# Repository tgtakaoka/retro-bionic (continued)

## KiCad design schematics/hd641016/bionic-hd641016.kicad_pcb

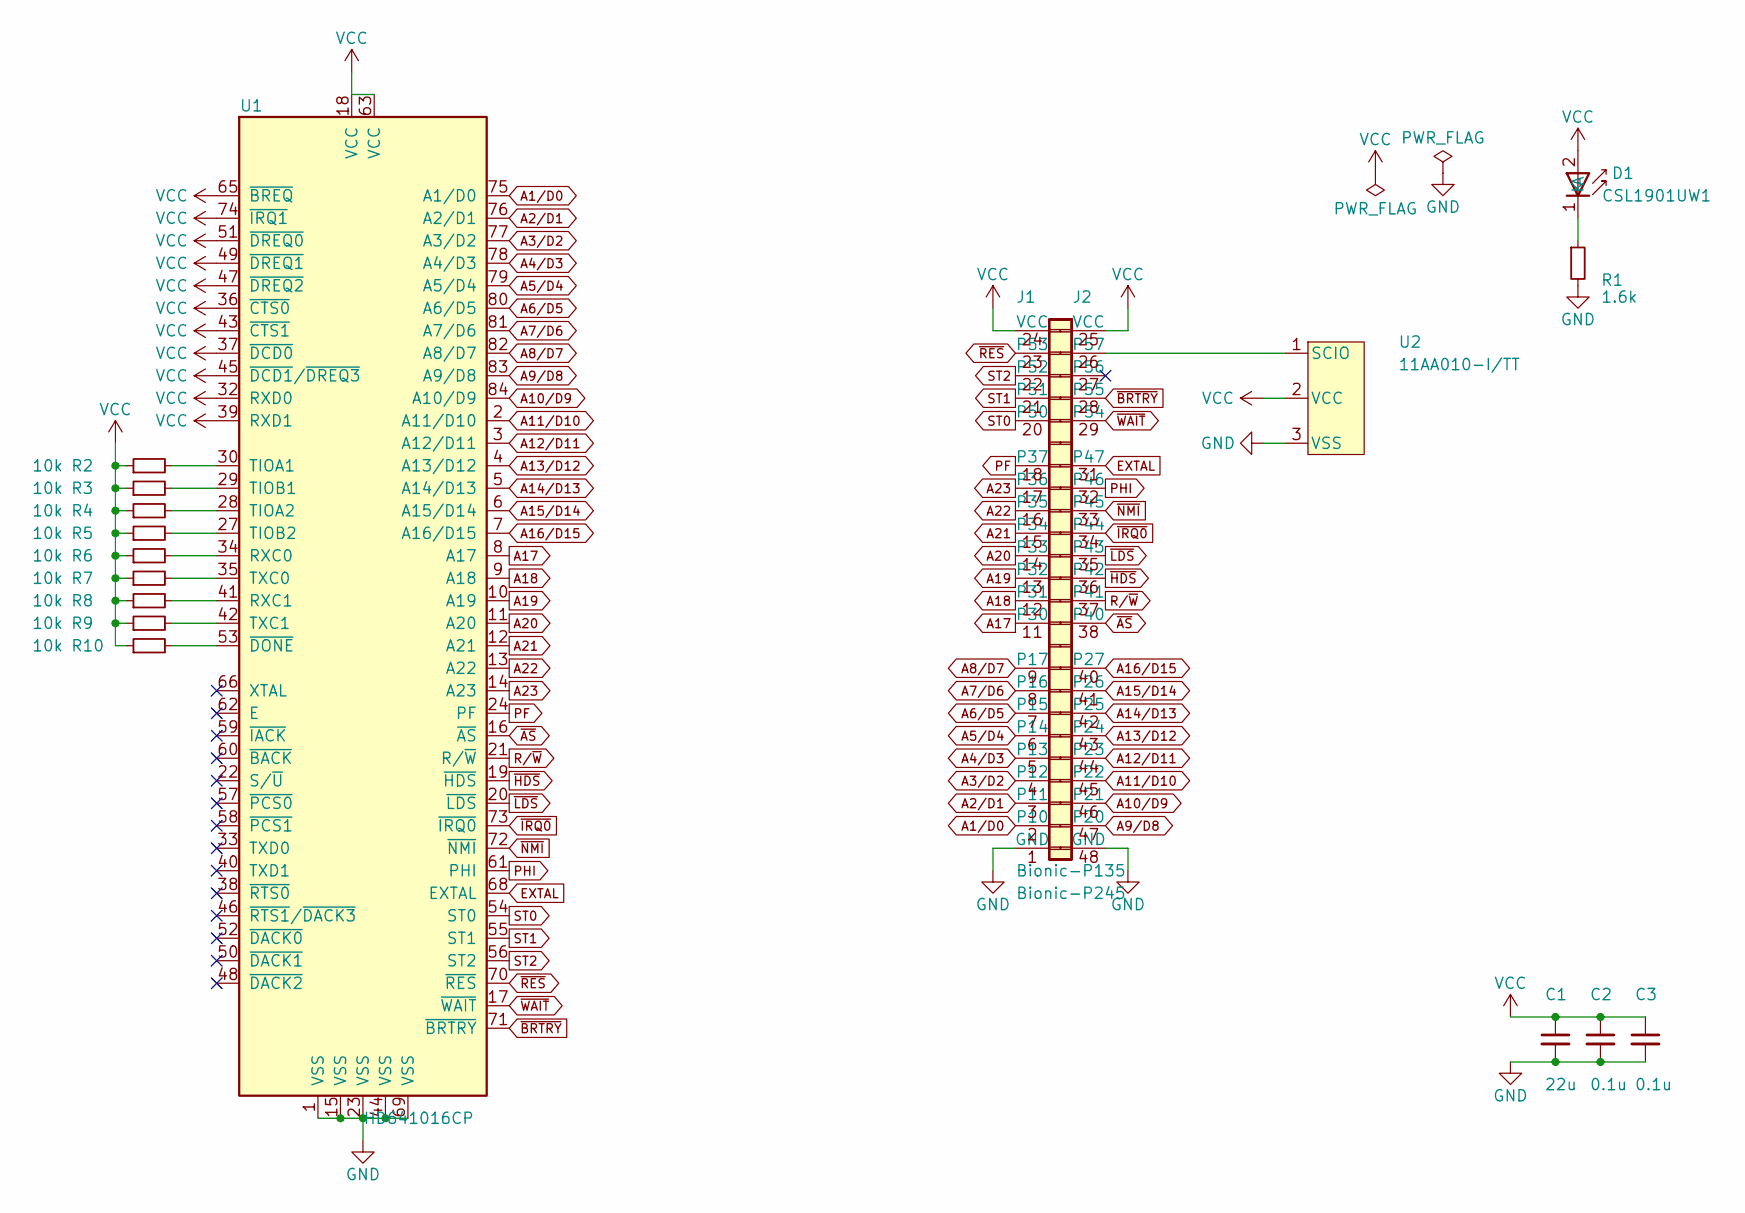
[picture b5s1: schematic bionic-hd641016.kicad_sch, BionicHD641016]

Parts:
C1: 22u; C_0603_1608Metric_Pad1.08x0.95mm_HandSolder
C2, C3: 0.1u; C_0603_1608Metric_Pad1.08x0.95mm_HandSolder
D1: CSL1901UW1; LED_CSL1901UW1_ROM-M
J1: Bionic-P135; Bionic-P135_SMT
J2: Bionic-P245; Bionic-P245_SMT
R1: 1.6k; R_0603_1608Metric_Pad0.98x0.95mm_HandSolder
R2, R3, R4, R5, R6, R7, R8, R9, R10: 10k; R_0603_1608Metric_Pad0.98x0.95mm_HandSolder
U1: HD641016CP; 848421B1RKTP
U2: 11AA010-I/TT; SOT-23_MC_MCH-M

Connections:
A1/D0: J1.2 (P10), U1.75 (A1/D0)
A2/D1: J1.3 (P11), U1.76 (A2/D1)
A3/D2: J1.4 (P12), U1.77 (A3/D2)
A4/D3: J1.5 (P13), U1.78 (A4/D3)
A5/D4: J1.6 (P14), U1.79 (A5/D4)
A6/D5: J1.7 (P15), U1.80 (A6/D5)
A7/D6: J1.8 (P16), U1.81 (A7/D6)
A8/D7: J1.9 (P17), U1.82 (A8/D7)
A9/D8: J2.47 (P20), U1.83 (A9/D8)
A10/D9: J2.46 (P21), U1.84 (A10/D9)
A11/D10: J2.45 (P22), U1.2 (A11/D10)
A12/D11: J2.44 (P23), U1.3 (A12/D11)
A13/D12: J2.43 (P24), U1.4 (A13/D12)
A14/D13: J2.42 (P25), U1.5 (A14/D13)
A15/D14: J2.41 (P26), U1.6 (A15/D14)
A16/D15: J2.40 (P27), U1.7 (A16/D15)
A17: J1.11 (P30), U1.8 (A17)
A18: J1.12 (P31), U1.9 (A18)
A19: J1.13 (P32), U1.10 (A19)
A20: J1.14 (P33), U1.11 (A20)
A21: J1.15 (P34), U1.12 (A21)
A22: J1.16 (P35), U1.13 (A22)
A23: J1.17 (P36), U1.14 (A23)
EXTAL: J2.31 (P47), U1.68 (EXTAL)
GND: C1.2, C2.2, C3.2, J1.1 (GND), J2.48 (GND), R1.2, U1.1 (VSS), U1.15 (VSS), U1.23 (VSS), U1.44 (VSS), U1.69 (VSS), U2.3 (VSS)
unnamed: D1.1 (K), R1.1
unnamed: J2.26 (P57), U2.1 (SCIO)
unnamed: R6.2, U1.34 (RXC0)
unnamed: R8.2, U1.41 (RXC1)
unnamed: R2.2, U1.30 (TIOA1)
unnamed: R4.2, U1.28 (TIOA2)
unnamed: R3.2, U1.29 (TIOB1)
unnamed: R5.2, U1.27 (TIOB2)
unnamed: R7.2, U1.35 (TXC0)
unnamed: R9.2, U1.42 (TXC1)
unnamed: R10.2, U1.53 (~DONE)
PF: J1.18 (P37), U1.24 (PF)
PHI: J2.32 (P46), U1.61 (PHI)
R/~W: J2.37 (P41), U1.21 (R/~W)
ST0: J1.20 (P50), U1.54 (ST0)
ST1: J1.21 (P51), U1.55 (ST1)
ST2: J1.22 (P52), U1.56 (ST2)
VCC: C1.1, C2.1, C3.1, D1.2 (A), J1.24 (VCC), J2.25 (VCC), R2.1, R3.1, R4.1, R5.1, R6.1, R7.1, R8.1, R9.1, R10.1, U1.18 (VCC), U1.32 (RXD0), U1.36 (~CTS0), U1.37 (~DCD0), U1.39 (RXD1), U1.43 (~CTS1), U1.45 (~DCD1/~DREQ3), U1.47 (~DREQ2), U1.49 (~DREQ1), U1.51 (~DREQ0), U1.63 (VCC), U1.65 (~BREQ), U1.74 (~IRQ1), U2.2 (VCC)
~AS: J2.38 (P40), U1.16 (~AS)
~BRTRY: J2.28 (P55), U1.71 (~BRTRY)
~HDS: J2.36 (P42), U1.19 (~HDS)
~IRQ0: J2.34 (P44), U1.73 (~IRQ0)
~LDS: J2.35 (P43), U1.20 (~LDS)
~NMI: J2.33 (P45), U1.72 (~NMI)
~RES: J1.23 (P53), U1.70 (~RES)
~WAIT: J2.29 (P54), U1.17 (~WAIT)

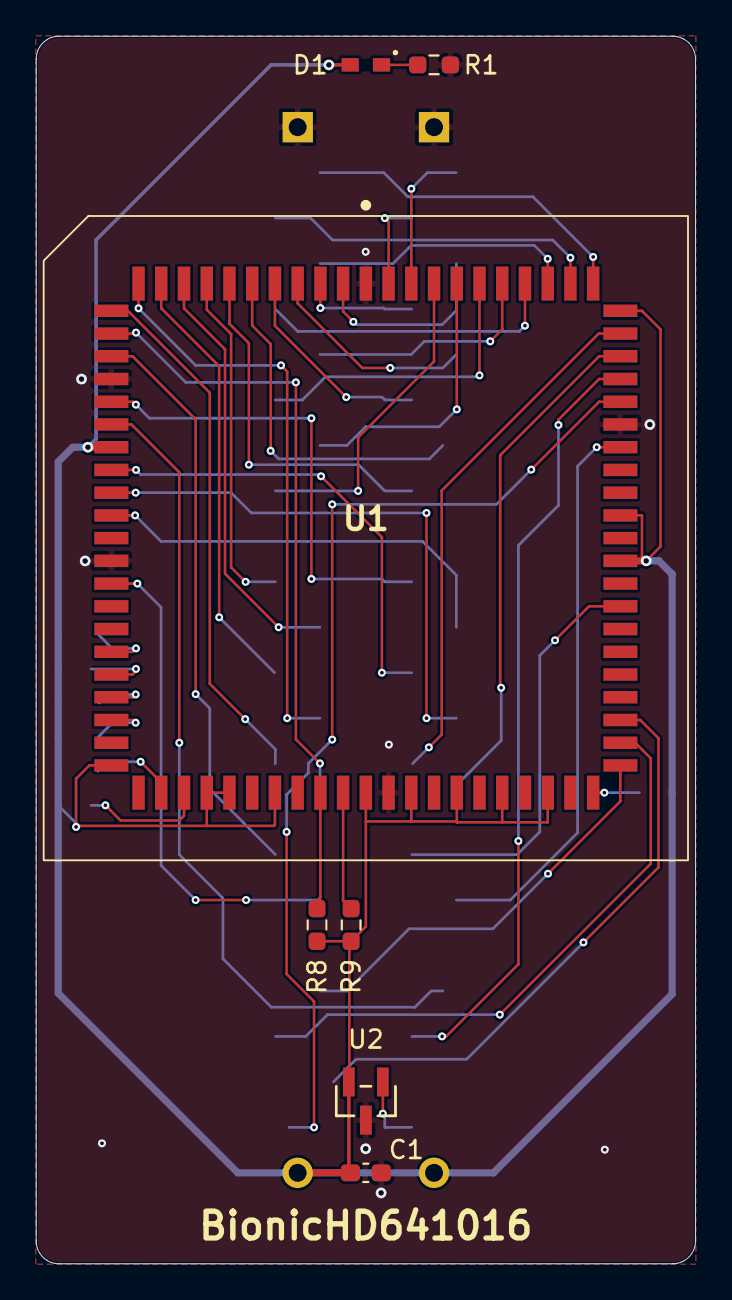
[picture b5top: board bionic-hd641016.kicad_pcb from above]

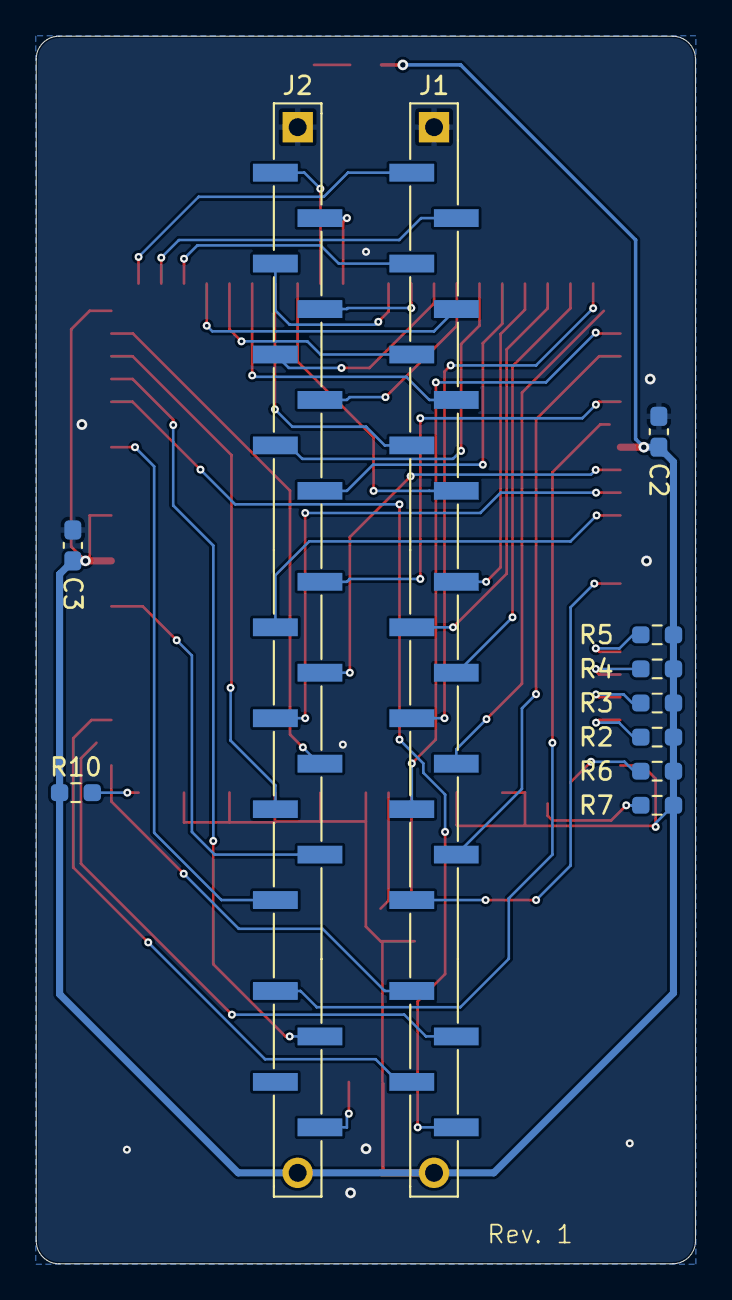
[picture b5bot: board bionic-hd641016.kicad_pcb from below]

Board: 2 copper layers, 36.8 x 68.6 mm, 18 parts (11 on the bottom side), 51 nets.

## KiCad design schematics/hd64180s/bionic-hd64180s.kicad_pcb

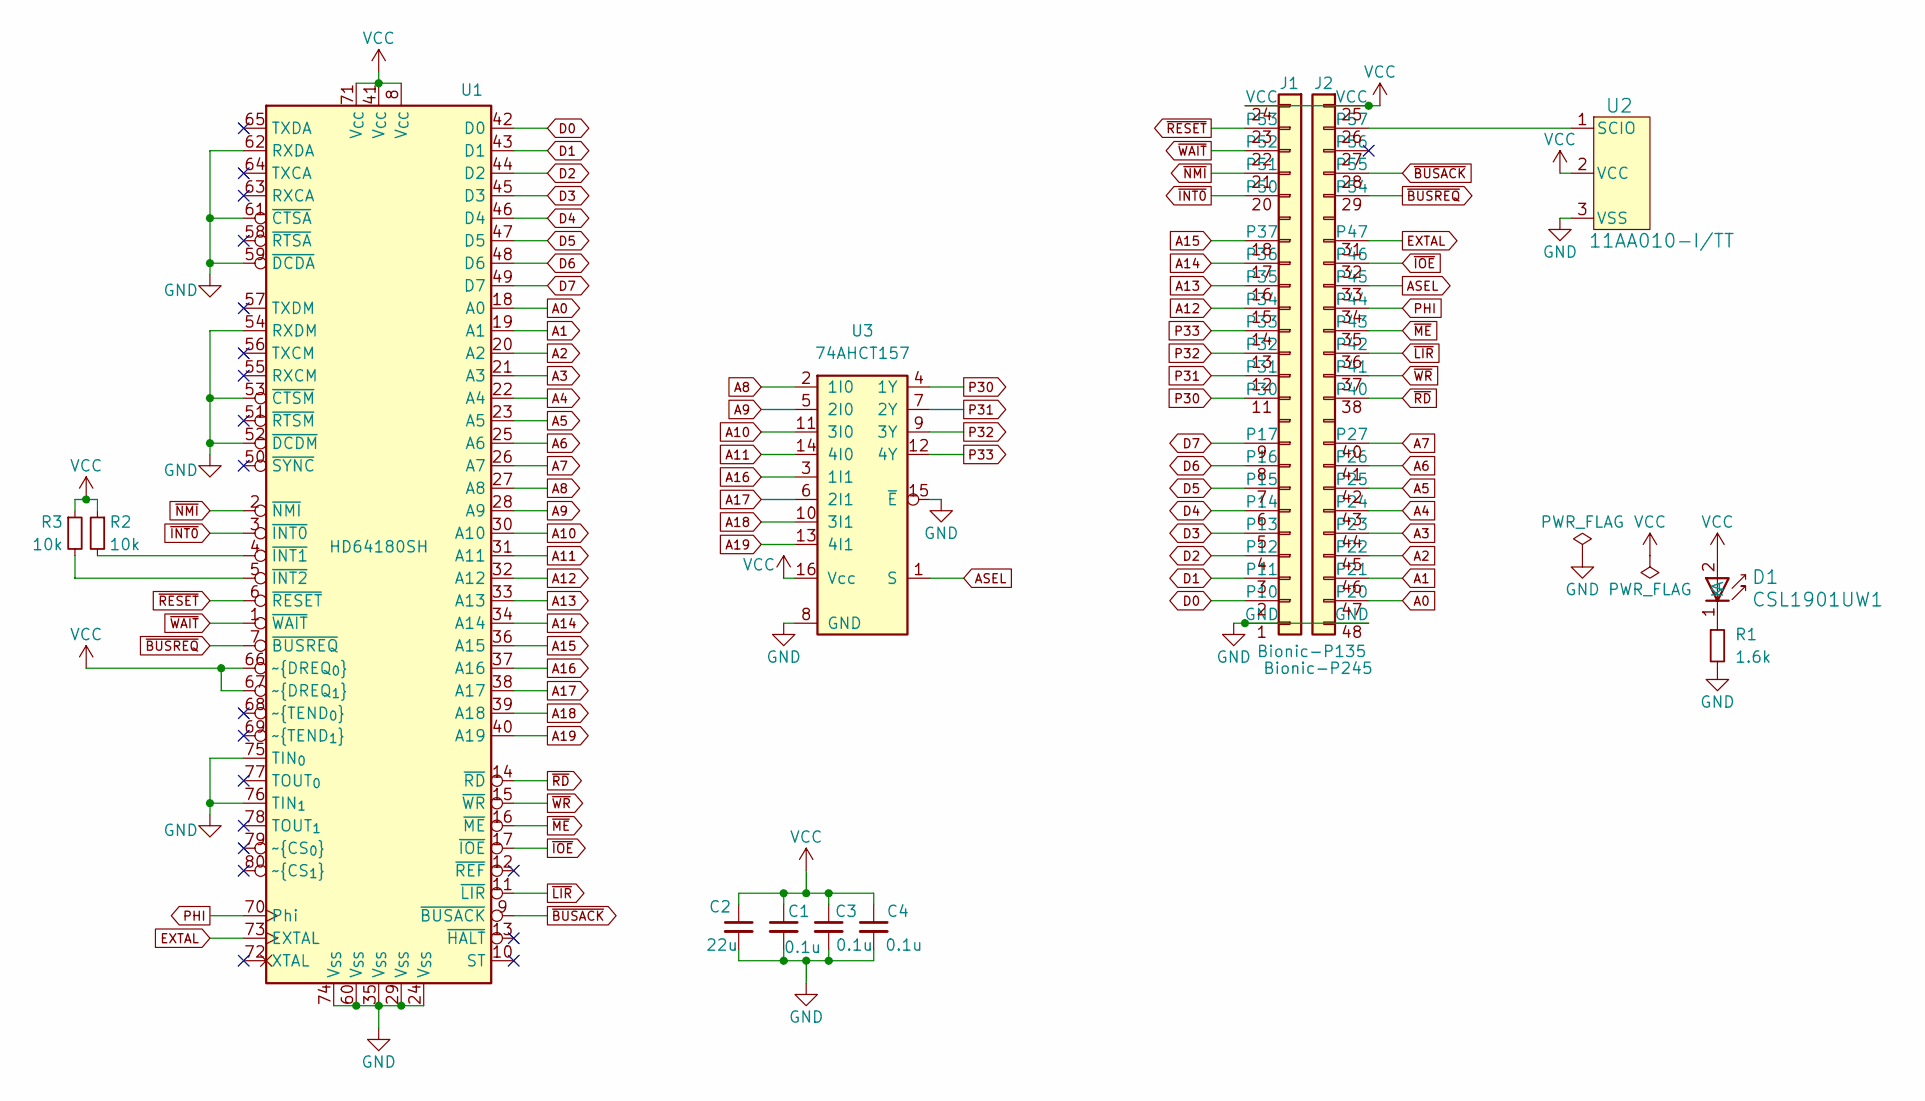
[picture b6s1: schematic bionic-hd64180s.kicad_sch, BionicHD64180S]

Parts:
C1, C3, C4: 0.1u; C_0603_1608Metric_Pad1.08x0.95mm_HandSolder
C2: 22u; C_0603_1608Metric_Pad1.08x0.95mm_HandSolder
D1: CSL1901UW1; LED_CSL1901UW1_ROM-M
J1: Bionic-P135; Bionic-P135_SMT
J2: Bionic-P245; Bionic-P245_SMT
R1: 1.6k; R_0603_1608Metric_Pad0.98x0.95mm_HandSolder
R2, R3: 10k; R_0603_1608Metric_Pad0.98x0.95mm_HandSolder
U1: HD64180SH; PQFP-80_14x14mm_P0.65mm
U2: 11AA010-I/TT; SOT-23_MC_MCH-M
U3: 74AHCT157; PW16-M

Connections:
A0: J2.47 (P20), U1.18 (A0)
A1: J2.46 (P21), U1.19 (A1)
A2: J2.45 (P22), U1.20 (A2)
A3: J2.44 (P23), U1.21 (A3)
A4: J2.43 (P24), U1.22 (A4)
A5: J2.42 (P25), U1.23 (A5)
A6: J2.41 (P26), U1.25 (A6)
A7: J2.40 (P27), U1.26 (A7)
A8: U1.27 (A8), U3.2 (1I0)
A9: U1.28 (A9), U3.5 (2I0)
A10: U1.30 (A10), U3.11 (3I0)
A11: U1.31 (A11), U3.14 (4I0)
A12: J1.15 (P34), U1.32 (A12)
A13: J1.16 (P35), U1.33 (A13)
A14: J1.17 (P36), U1.34 (A14)
A15: J1.18 (P37), U1.36 (A15)
A16: U1.37 (A16), U3.3 (1I1)
A17: U1.38 (A17), U3.6 (2I1)
A18: U1.39 (A18), U3.10 (3I1)
A19: U1.40 (A19), U3.13 (4I1)
ASEL: J2.33 (P45), U3.1 (S)
D0: J1.2 (P10), U1.42 (D0)
D1: J1.3 (P11), U1.43 (D1)
D2: J1.4 (P12), U1.44 (D2)
D3: J1.5 (P13), U1.45 (D3)
D4: J1.6 (P14), U1.46 (D4)
D5: J1.7 (P15), U1.47 (D5)
D6: J1.8 (P16), U1.48 (D6)
D7: J1.9 (P17), U1.49 (D7)
EXTAL: J2.31 (P47), U1.73 (EXTAL)
GND: C1.2, C2.2, C3.2, C4.2, J1.1 (GND), J2.48 (GND), R1.2, U1.24 (V_{SS}), U1.29 (V_{SS}), U1.35 (V_{SS}), U1.52 (~DCDM), U1.53 (~CTSM), U1.54 (RXDM), U1.59 (~DCDA), U1.60 (V_{SS}), U1.61 (~CTSA), U1.62 (RXDA), U1.74 (V_{SS}), U1.75 (TIN_{0}), U1.76 (TIN_{1}), U2.3 (VSS), U3.8 (GND), U3.15 (~E)
unnamed: D1.1 (K), R1.1
unnamed: J2.26 (P57), U2.1 (SCIO)
unnamed: R2.2, U1.4 (~INT1)
unnamed: R3.2, U1.5 (~INT2)
P30: J1.11 (P30), U3.4 (1Y)
P31: J1.12 (P31), U3.7 (2Y)
P32: J1.13 (P32), U3.9 (3Y)
P33: J1.14 (P33), U3.12 (4Y)
PHI: J2.34 (P44), U1.70 (Phi)
VCC: C1.1, C2.1, C3.1, C4.1, D1.2 (A), J1.24 (VCC), J2.25 (VCC), R2.1, R3.1, U1.8 (V_{CC}), U1.41 (V_{CC}), U1.66 (~DREQ_{0}), U1.67 (~DREQ_{1}), U1.71 (V_{CC}), U2.2 (VCC), U3.16 (Vcc)
~BUSACK: J2.28 (P55), U1.9 (~BUSACK)
~BUSREQ: J2.29 (P54), U1.7 (~BUSREQ)
~INT0: J1.20 (P50), U1.3 (~INT0)
~IOE: J2.32 (P46), U1.17 (~IOE)
~LIR: J2.36 (P42), U1.11 (~LIR)
~ME: J2.35 (P43), U1.16 (~ME)
~NMI: J1.21 (P51), U1.2 (~NMI)
~RD: J2.38 (P40), U1.14 (~RD)
~RESET: J1.23 (P53), U1.6 (~RESET)
~WAIT: J1.22 (P52), U1.1 (~WAIT)
~WR: J2.37 (P41), U1.15 (~WR)

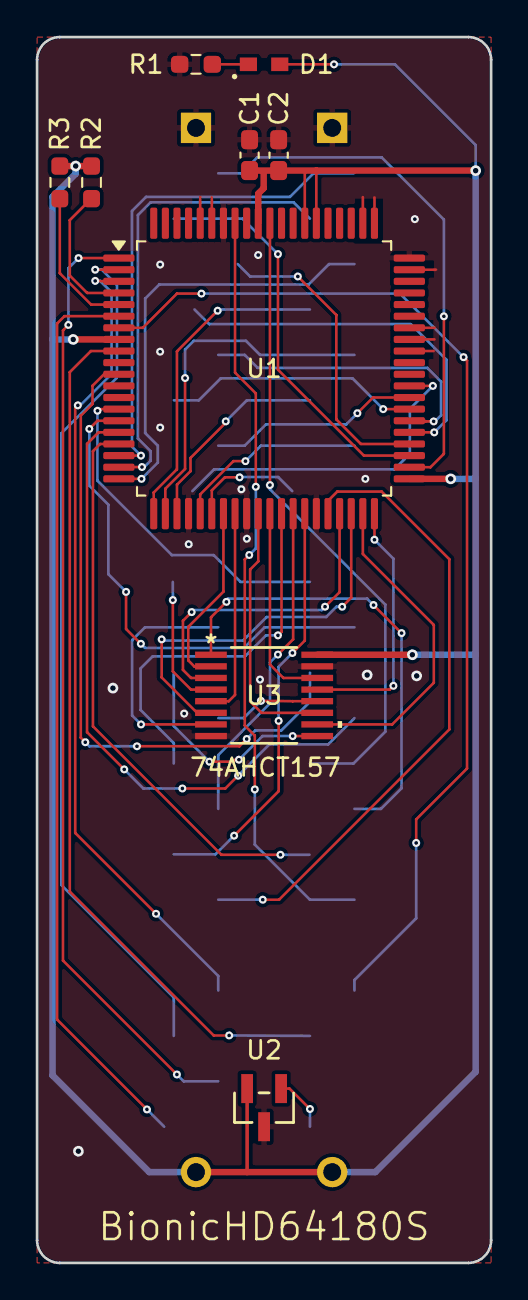
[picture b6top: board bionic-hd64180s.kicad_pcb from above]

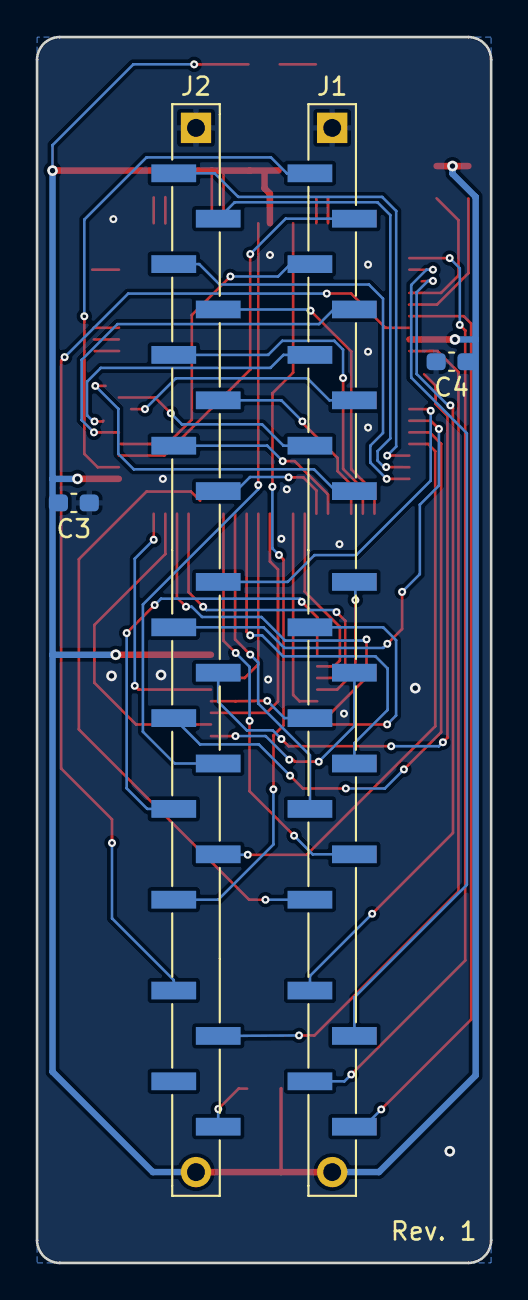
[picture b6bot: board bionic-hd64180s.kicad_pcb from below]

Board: 2 copper layers, 25.4 x 68.6 mm, 13 parts (4 on the bottom side), 52 nets.

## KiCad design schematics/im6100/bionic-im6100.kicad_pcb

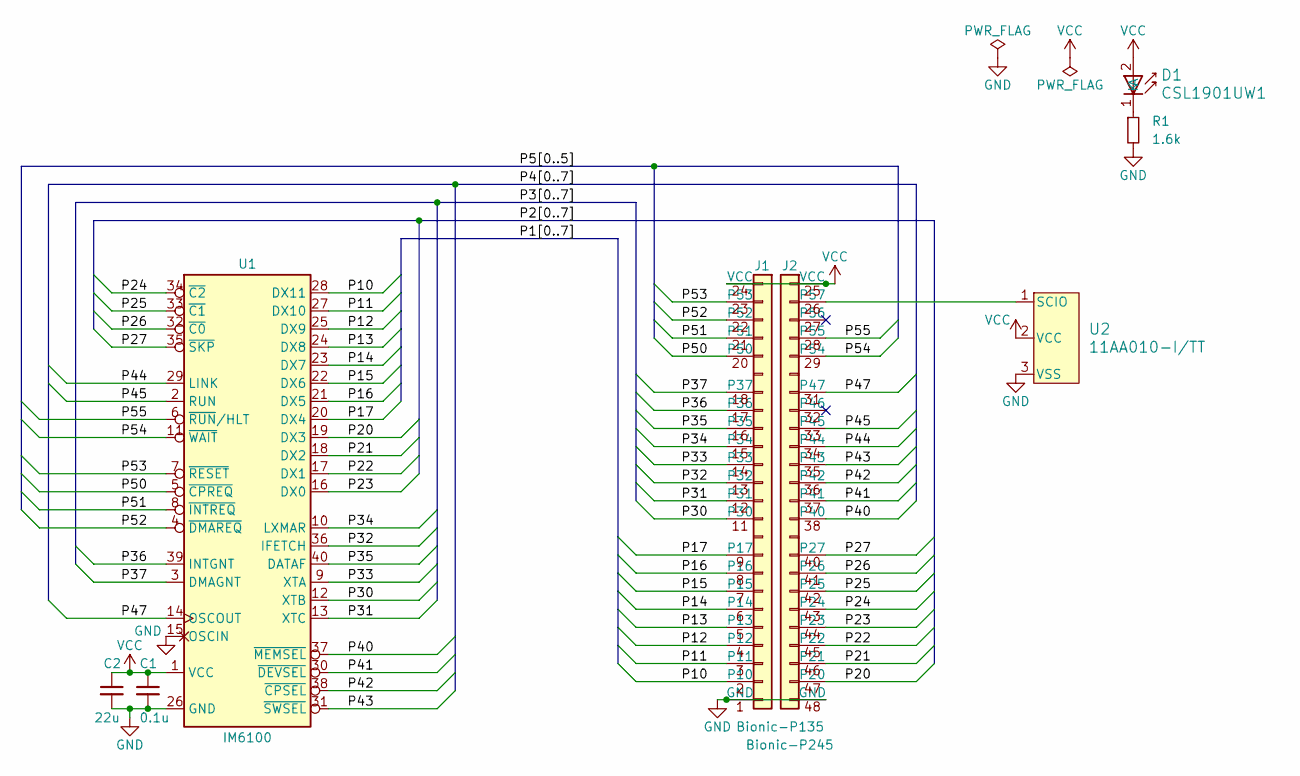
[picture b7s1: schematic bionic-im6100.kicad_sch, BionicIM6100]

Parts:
C1: 0.1u; C_0603_1608Metric_Pad1.08x0.95mm_HandSolder
C2: 22u; C_0603_1608Metric_Pad1.08x0.95mm_HandSolder
D1: CSL1901UW1; LED_CSL1901UW1_ROM-M
J1: Bionic-P135; Bionic-P135_THT
J2: Bionic-P245; Bionic-P245_THT
R1: 1.6k; R_0603_1608Metric_Pad0.98x0.95mm_HandSolder
U1: IM6100; DIP-40_W15.24mm_Socket
U2: 11AA010-I/TT; SOT-23_MC_MCH-M

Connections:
/P10: J1.2 (P10), U1.28 (DX11)
/P11: J1.3 (P11), U1.27 (DX10)
/P12: J1.4 (P12), U1.25 (DX9)
/P13: J1.5 (P13), U1.24 (DX8)
/P14: J1.6 (P14), U1.23 (DX7)
/P15: J1.7 (P15), U1.22 (DX6)
/P16: J1.8 (P16), U1.21 (DX5)
/P17: J1.9 (P17), U1.20 (DX4)
/P20: J2.47 (P20), U1.19 (DX3)
/P21: J2.46 (P21), U1.18 (DX2)
/P22: J2.45 (P22), U1.17 (DX1)
/P23: J2.44 (P23), U1.16 (DX0)
/P24: J2.43 (P24), U1.34 (~C2)
/P25: J2.42 (P25), U1.33 (~C1)
/P26: J2.41 (P26), U1.32 (~C0)
/P27: J2.40 (P27), U1.35 (~SKP)
/P30: J1.11 (P30), U1.12 (XTB)
/P31: J1.12 (P31), U1.13 (XTC)
/P32: J1.13 (P32), U1.36 (IFETCH)
/P33: J1.14 (P33), U1.9 (XTA)
/P34: J1.15 (P34), U1.10 (LXMAR)
/P35: J1.16 (P35), U1.40 (DATAF)
/P36: J1.17 (P36), U1.39 (INTGNT)
/P37: J1.18 (P37), U1.3 (DMAGNT)
/P40: J2.38 (P40), U1.37 (~MEMSEL)
/P41: J2.37 (P41), U1.30 (~DEVSEL)
/P42: J2.36 (P42), U1.38 (~CPSEL)
/P43: J2.35 (P43), U1.31 (~SWSEL)
/P44: J2.34 (P44), U1.29 (LINK)
/P45: J2.33 (P45), U1.2 (RUN)
/P47: J2.31 (P47), U1.14 (OSCOUT)
/P50: J1.20 (P50), U1.5 (~CPREQ)
/P51: J1.21 (P51), U1.8 (~INTREQ)
/P52: J1.22 (P52), U1.4 (~DMAREQ)
/P53: J1.23 (P53), U1.7 (~RESET)
/P54: J2.29 (P54), U1.11 (~WAIT)
/P55: J2.28 (P55), U1.6 (~RUN/HLT)
GND: C1.2, C2.2, J1.1 (GND), J2.48 (GND), R1.2, U1.15 (OSCIN), U1.26 (GND), U2.3 (VSS)
unnamed: D1.1 (K), R1.1
unnamed: J2.26 (P57), U2.1 (SCIO)
VCC: C1.1, C2.1, D1.2 (A), J1.24 (VCC), J2.25 (VCC), U1.1 (VCC), U2.2 (VCC)

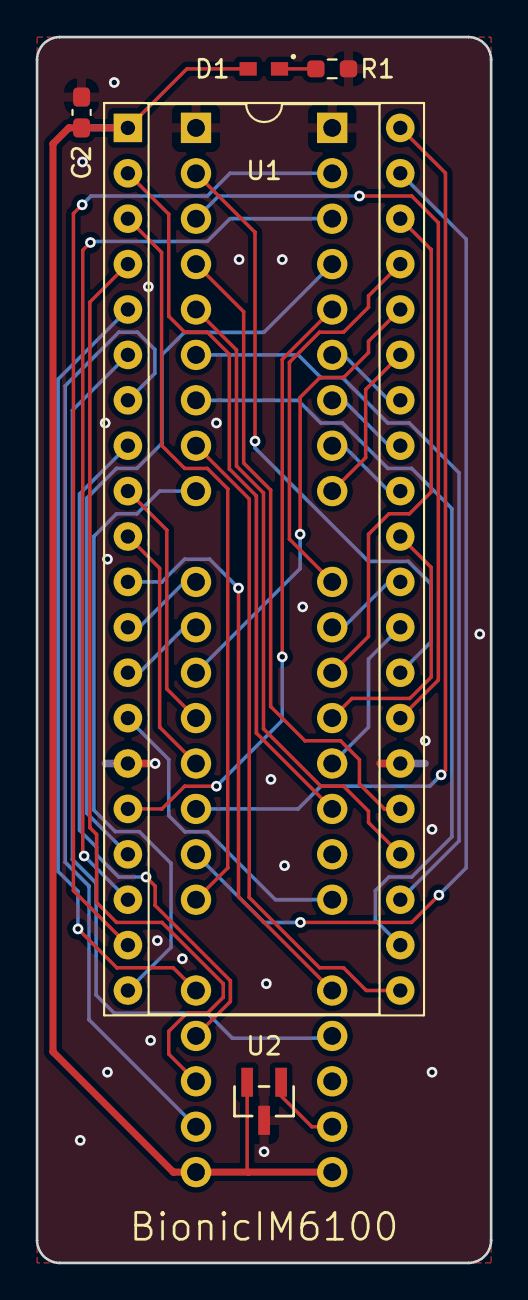
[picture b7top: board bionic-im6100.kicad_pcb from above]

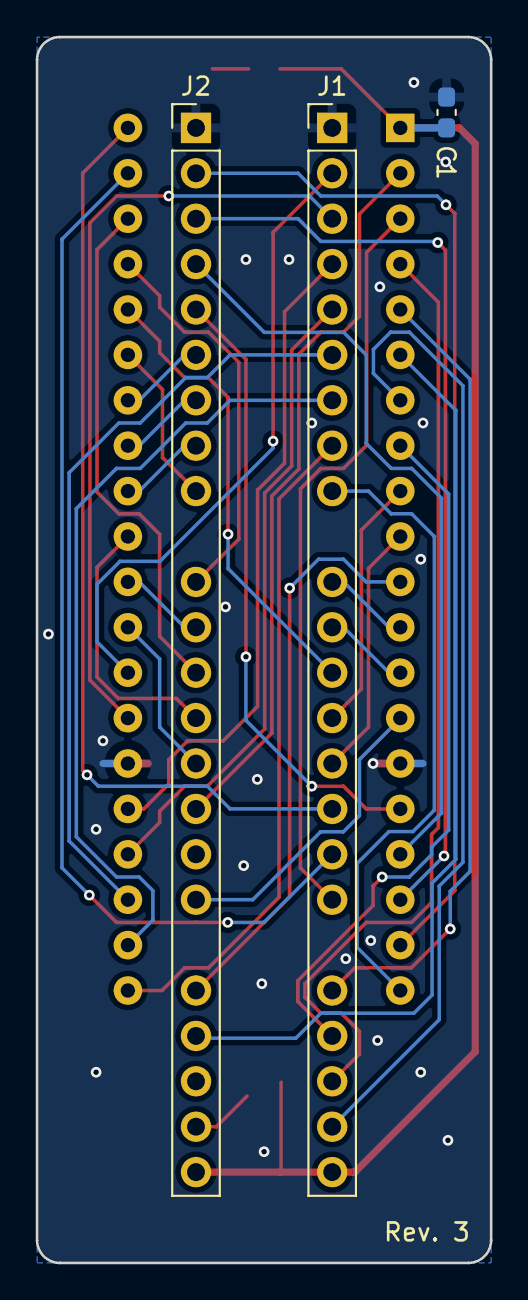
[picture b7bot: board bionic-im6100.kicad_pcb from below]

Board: 2 copper layers, 25.4 x 68.6 mm, 8 parts (3 on the bottom side), 41 nets.

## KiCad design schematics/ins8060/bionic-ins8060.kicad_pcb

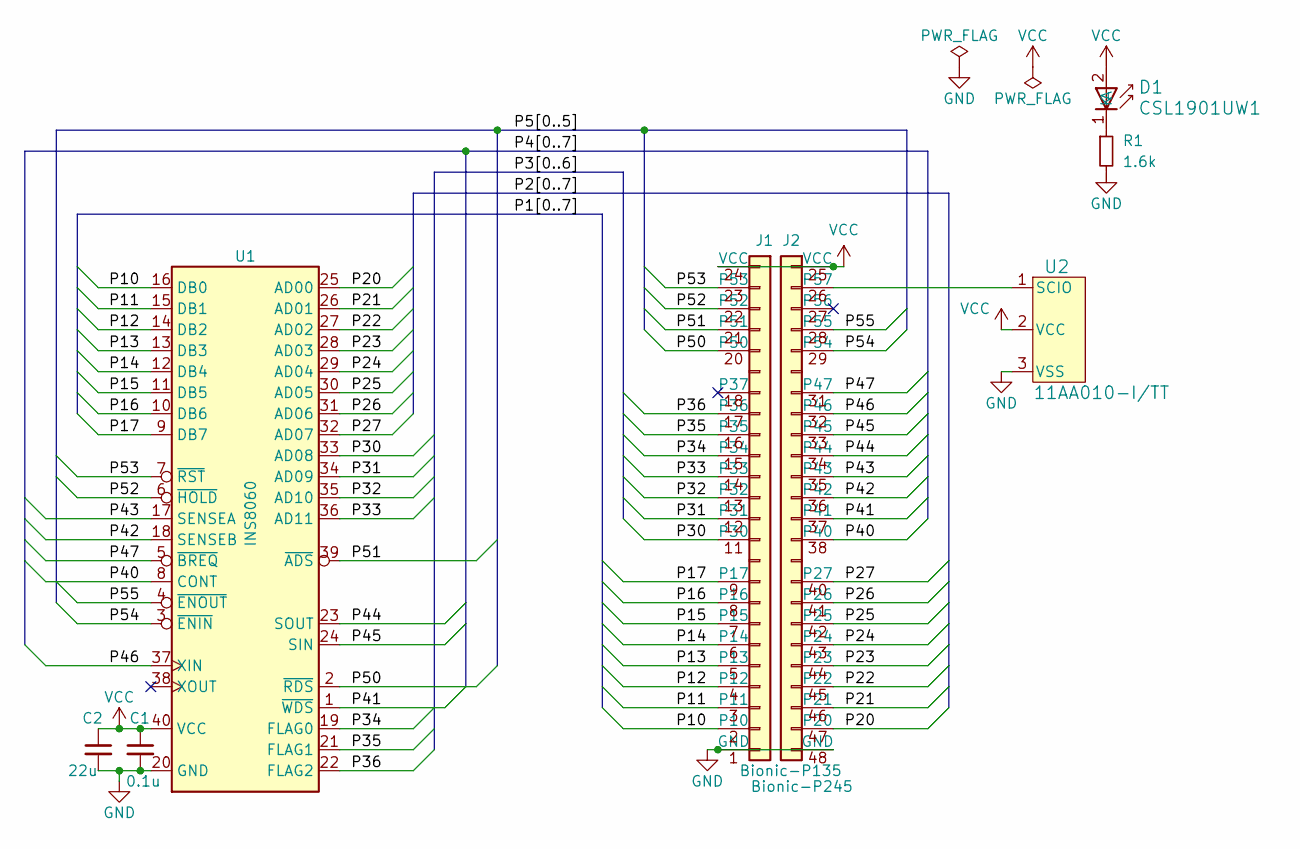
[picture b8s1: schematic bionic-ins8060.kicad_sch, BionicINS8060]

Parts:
C1: 0.1u; C_0603_1608Metric_Pad1.08x0.95mm_HandSolder
C2: 22u; C_0603_1608Metric_Pad1.08x0.95mm_HandSolder
D1: CSL1901UW1; LED_CSL1901UW1_ROM-M
J1: Bionic-P135; Bionic-P135_THT
J2: Bionic-P245; Bionic-P245_THT
R1: 1.6k; R_0603_1608Metric_Pad0.98x0.95mm_HandSolder
U1: INS8060; DIP-40_W15.24mm_Socket
U2: 11AA010-I/TT; SOT-23_MC_MCH-M

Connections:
/P10: J1.2 (P10), U1.16 (DB0)
/P11: J1.3 (P11), U1.15 (DB1)
/P12: J1.4 (P12), U1.14 (DB2)
/P13: J1.5 (P13), U1.13 (DB3)
/P14: J1.6 (P14), U1.12 (DB4)
/P15: J1.7 (P15), U1.11 (DB5)
/P16: J1.8 (P16), U1.10 (DB6)
/P17: J1.9 (P17), U1.9 (DB7)
/P20: J2.47 (P20), U1.25 (AD00)
/P21: J2.46 (P21), U1.26 (AD01)
/P22: J2.45 (P22), U1.27 (AD02)
/P23: J2.44 (P23), U1.28 (AD03)
/P24: J2.43 (P24), U1.29 (AD04)
/P25: J2.42 (P25), U1.30 (AD05)
/P26: J2.41 (P26), U1.31 (AD06)
/P27: J2.40 (P27), U1.32 (AD07)
/P30: J1.11 (P30), U1.33 (AD08)
/P31: J1.12 (P31), U1.34 (AD09)
/P32: J1.13 (P32), U1.35 (AD10)
/P33: J1.14 (P33), U1.36 (AD11)
/P34: J1.15 (P34), U1.19 (FLAG0)
/P35: J1.16 (P35), U1.21 (FLAG1)
/P36: J1.17 (P36), U1.22 (FLAG2)
/P40: J2.38 (P40), U1.8 (CONT)
/P41: J2.37 (P41), U1.1 (~WDS)
/P42: J2.36 (P42), U1.18 (SENSEB)
/P43: J2.35 (P43), U1.17 (SENSEA)
/P44: J2.34 (P44), U1.23 (SOUT)
/P45: J2.33 (P45), U1.24 (SIN)
/P46: J2.32 (P46), U1.37 (XIN)
/P47: J2.31 (P47), U1.5 (~BREQ)
/P50: J1.20 (P50), U1.2 (~RDS)
/P51: J1.21 (P51), U1.39 (~ADS)
/P52: J1.22 (P52), U1.6 (~HOLD)
/P53: J1.23 (P53), U1.7 (~RST)
/P54: J2.29 (P54), U1.3 (~ENIN)
/P55: J2.28 (P55), U1.4 (~ENOUT)
GND: C1.2, C2.2, J1.1 (GND), J2.48 (GND), R1.2, U1.20 (GND), U2.3 (VSS)
unnamed: D1.1 (K), R1.1
unnamed: J2.26 (P57), U2.1 (SCIO)
VCC: C1.1, C2.1, D1.2 (A), J1.24 (VCC), J2.25 (VCC), U1.40 (VCC), U2.2 (VCC)

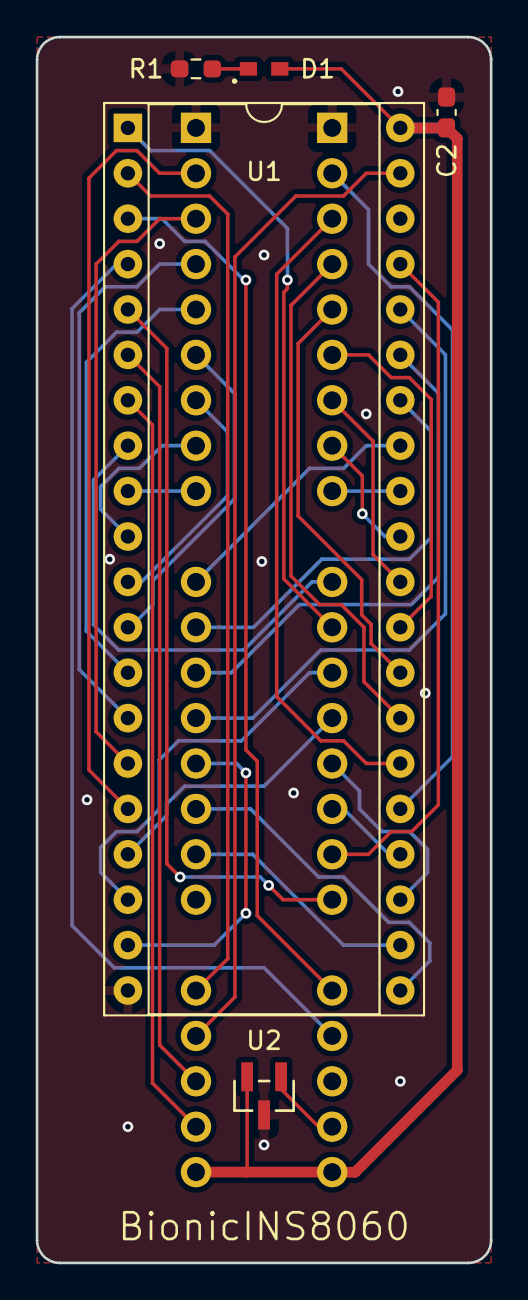
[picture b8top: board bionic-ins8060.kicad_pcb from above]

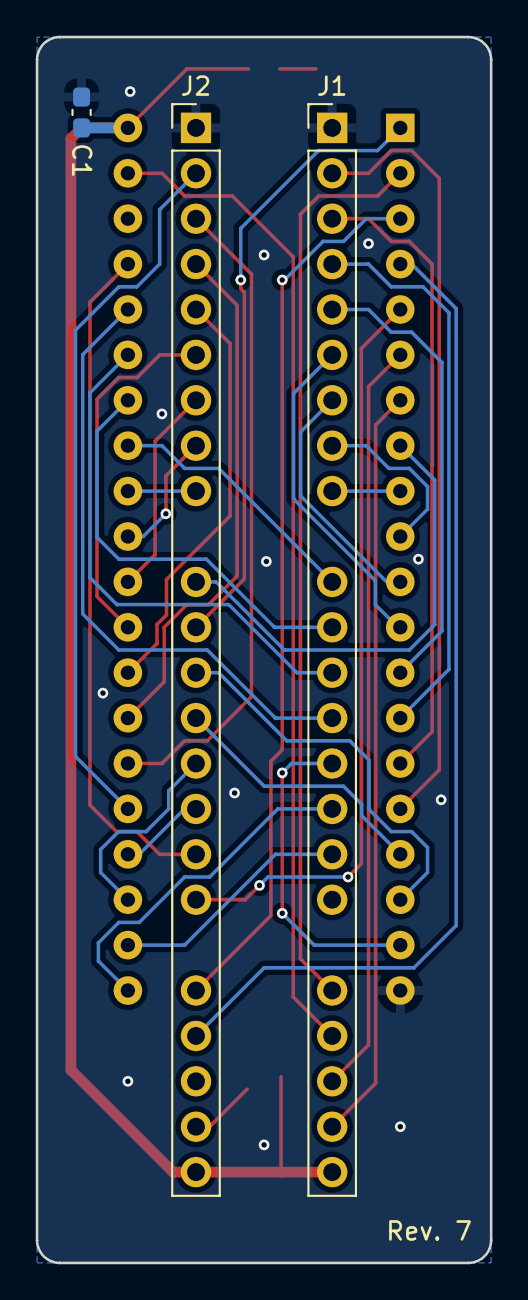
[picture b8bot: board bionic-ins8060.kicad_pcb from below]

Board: 2 copper layers, 25.4 x 68.6 mm, 8 parts (3 on the bottom side), 41 nets.
